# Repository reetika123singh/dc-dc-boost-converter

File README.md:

# DC-DC Boost Converter — Design & Closed-Loop Simulation

A 5V-to-12V boost converter designed and simulated for closed-loop steady-state voltage regulation, with a custom KiCad schematic and PCB layout, and a MATLAB/Simulink model of the control loop.

## Key Specifications

| Parameter | Value |
|---|---|
| Input Voltage (Vin) | 5 V |
| Output Voltage (Vout) | 12 V |
| Switching Frequency (fs) | 100 kHz |
| Target Load Current (Iout) | 1 A – 1.5 A (peak 2 A) |
| Control Scheme | Closed-loop PI control with dynamic PWM duty cycle generation |

## Design Approach

- The converter operates at 100 kHz switching frequency, chosen to minimize the size and weight of the inductor and capacitor while keeping power loss and heat low. In space hardware, keeping components lightweight is critical, but cooling in a vacuum is difficult. Operating at 100 kHz provides the ideal balance: it allows for a compact PCB footprint while delivering a clean output.
- Inductor and output capacitor values were selected to keep output voltage ripple under 1% and ensure continuous conduction mode at the target load range.
- The PI controller gains (Kp = 0.01, Ki = 50) were tuned to regulate output voltage against load transients.
- PWM duty cycle is generated dynamically based on the PI controller's error signal between reference (12V) and sensed output voltage.

## Repository Structure

- `DC-DC Boost converter/` — KiCad schematic (`.kicad_sch`), PCB layout (`.kicad_pcb`), and project files.
- `Simulation/` — MATLAB/Simulink closed-loop model (`.slx`) and simulation setup files.

## How to Run the Simulation

1. Open MATLAB and navigate to the `Simulation/` directory.
2. Open the `.slx` model in Simulink.
3. Run the simulation to observe the output voltage settling to 12V and the switching/PWM waveforms.

## PCB

## Results

1. **Steady-state output voltage:** 12 V
2. **Settling time:** 50 ms
3. **Voltage ripple:** 15.91 mV / 0.13%

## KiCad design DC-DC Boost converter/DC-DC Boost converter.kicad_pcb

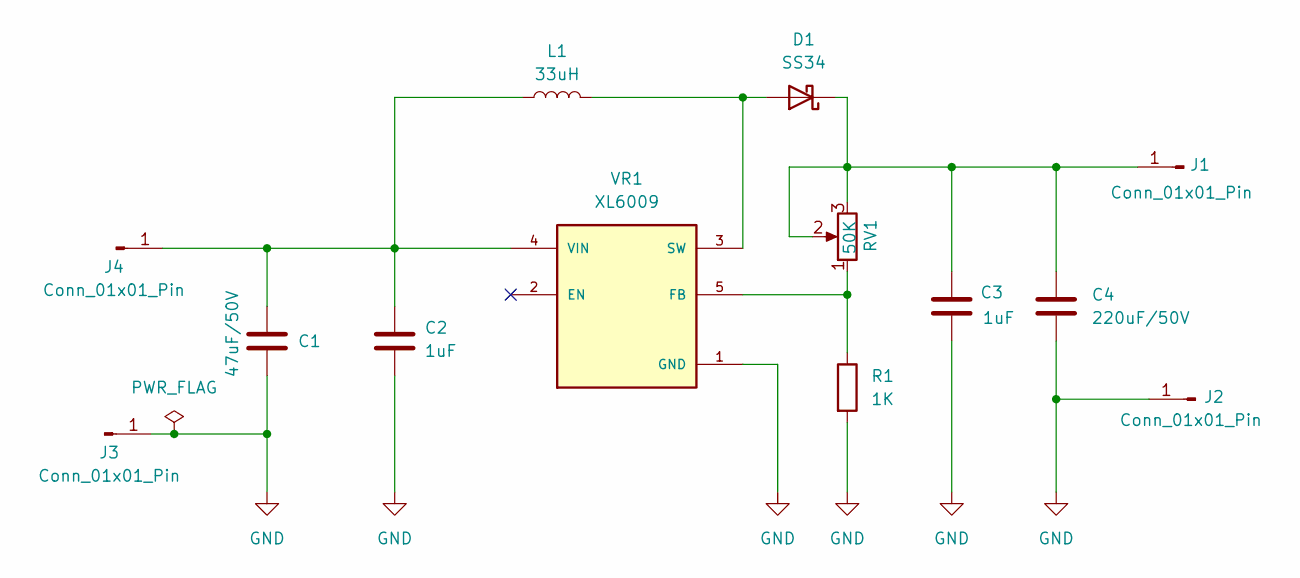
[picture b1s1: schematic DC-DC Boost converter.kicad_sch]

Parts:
C1: 47uF/50V; C_Radial_D6.3mm_H11.0mm_P2.50mm
C2, C3: 1uF; C_0805_2012Metric
C4: 220uF/50V; C_Radial_D6.3mm_H11.0mm_P2.50mm
D1: SS34; D_SMA
J1, J2, J3, J4: Conn_01x01_Pin; PinHeader_1x01_P2.54mm_Vertical
L1: 33uH; L_12x12mm_H8mm
R1: 1K; R_1206_3216Metric
RV1: 50K; Potentiometer_Bourns_3296W_Vertical
VR1: XL6009; DPAK170P1435X465-6N; PARTREV 1.1

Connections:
GND: C1.2, C2.2, C3.2, C4.2, J2.1, J3.1, R1.2, VR1.1 (GND)
unnamed: D1.2 (A), L1.2, VR1.3 (SW), VR1.6 (SW)
unnamed: C3.1, C4.1, D1.1 (K), J1.1, RV1.2, RV1.3
unnamed: C1.1, C2.1, J4.1, L1.1, VR1.4 (VIN)
unnamed: R1.1, RV1.1, VR1.5 (FB)

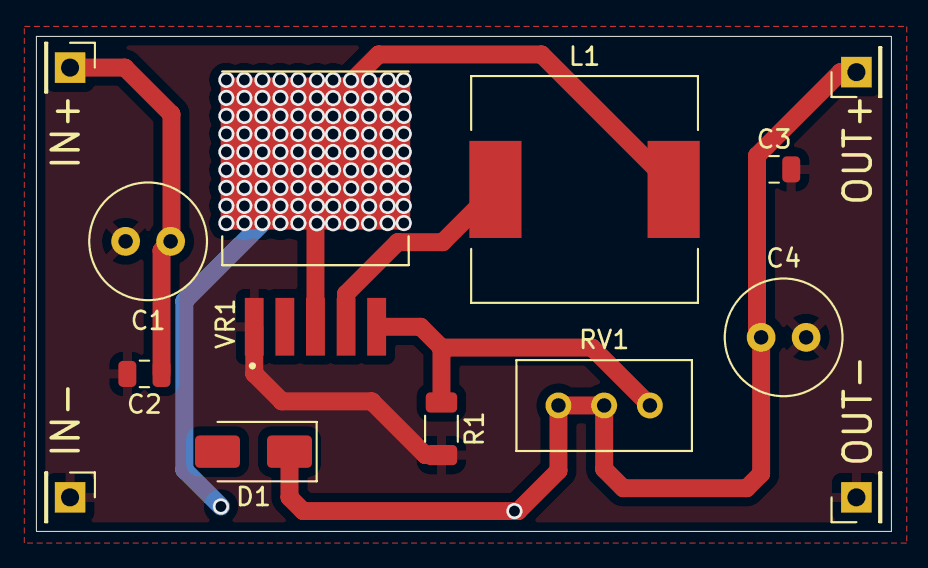
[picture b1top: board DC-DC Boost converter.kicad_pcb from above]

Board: 2 copper layers, 47.5 x 27.5 mm, 13 parts (0 on the bottom side), 5 nets.
